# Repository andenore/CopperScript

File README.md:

# CopperScript

**PCB design as code. Hardware intent, written in code.**

CopperScript is a strongly typed language and compiler for PCB connectivity,
electrical intent, mechanical geometry and physical constraints. Describe
components, peripheral selection, nets, supply domains, board shape and placement
intent in readable `.copper` source. Check electrical rules, resolve versioned
library parts, edit mechanics and floorplans visually, and inspect experimental
routing and native KiCad exports.

[Project website](https://andenore.github.io/CopperScript/) ·
[Language reference](docs/language-reference.md) ·
[Examples](examples/README.md) ·
[CopperAssetTracker](https://github.com/andenore/CopperAssetTracker)

LLM agents: start with `copper agent-guide`, then request only the topics and
library contracts needed for the task. Contributors also follow [AGENTS.md](AGENTS.md).
The [documentation index](docs/README.md) routes tasks to current references;
[TODO.md](TODO.md) tracks unfinished work.

## More than connections

A capacitor protects a particular pin. A switching converter has a critical
current loop. A radio needs reference geometry and a return path. CopperScript
makes supported intent explicit alongside the connections, with reusable
engineering definitions and inspectable intermediate representations.

```copper
component C_MCU: CAPACITOR {
    value = 100nF;
    footprint = "Capacitor_SMD:C_0402_1005Metric";
    role = decoupling;
    decouples = "U_MCU.VDD";
}
```

This excerpt from the tracker composition associates a bypass capacitor with
its supply pin. The association survives compilation and informs generic
decoupling placement and surface-feed decisions. It is not a complete board.

## Mechanical design and constraints

Define board shape and fit in the same version-controlled source as the circuit:
rectangular, circular, polygonal and supported curved outlines; cutouts; mounting
holes and slots; placement and copper keepouts. Named datums and edge/pad
attachments locate connectors precisely. Declared component heights, enclosure
limits and assembly-access regions express supported fit requirements; pinned
DXF drawings provide read-only reference guides.

Placement constraints capture fixed position, rotation and side, allowed angles,
placement regions, distance limits, alignment and groups. Routing constraints
describe widths, clearances, permitted layers, differential pairs and length
matching. Supported constraints reach physical IR and their placement, routing
or verification consumers; reports retain unresolved requirements and external
evidence obligations.

This excerpt from [the mechanical editor demo](examples/mechanical_editor_demo/board.copper)
defines a board outline, a mounting hole and a component pose. The complete
example supplies the component declarations and nets:

```copper
mechanical {
    outline rectangle { width = 40mm; height = 30mm; }
    hole H1 {
        position = (3mm, 3mm); diameter = 2.2mm;
        head_clearance_radius = 2mm;
    }
}
constraint fixed_placement(R_ANCHOR) {
    x = 7mm; y = 8mm;
    rotation = 0; side = front;
}
```

The browser-based mechanical editor shows actual pads, courtyards, board material
and ratsnest guides. Preview automatic placement, drag or enter exact poses,
measure geometry and deliberately lock placement intent. Review the source diff
and explicitly save geometry or constraint changes back to `.copper`, with
undo/redo.
Temporary placement previews stay temporary until you save explicit intent;
imported profile definitions retain their library ownership.

```console
copper edit-mechanical examples/mechanical_editor_demo/board.copper
```

Resolve the example's real KiCad footprints before opening the editor. See
[mechanical source](docs/mechanical-language.md),
[the editor workflow](docs/mechanical-editor.md),
[reusable board profiles](docs/mechanical-profiles.md),
[constraint syntax and coverage](docs/language-reference.md#constraints) and
[VS Code setup](integrations/vscode/README.md). Supported mechanical checks do
not establish a full 3D enclosure fit or manufacturing qualification.

## See a complete design

[CopperAssetTracker](https://github.com/andenore/CopperAssetTracker) combines
an STM32 host, cellular connectivity, GNSS, Bluetooth and motion sensing on a
six-layer board. The recorded 2026-10-11 modem-power review has 91 components and
75 physical nets, with zero native DRC violations and zero unconnected items.
These are results for that recorded candidate, not a success guarantee for other
boards or a production approval. Routing remains experimental; RF, power,
battery, assembly, CAM and prototype qualification remain open.

Inspect the [snapshot provenance](site/assets/snapshot.json),
[current board status](https://github.com/andenore/CopperAssetTracker/blob/main/docs/validation.md)
and [revision reproduction guide](https://github.com/andenore/CopperAssetTracker/blob/main/revisions/modem-power-v1/README.md).
The picture is native KiCad output, not a photograph of assembled hardware.

## Three repositories, one workflow

| Repository | Owns |
| --- | --- |
| CopperScript | Language/compiler, electrical and physical checks, mechanical editor, constraint-driven placement/routing and KiCad export |
| [CopperLib](https://github.com/andenore/CopperLib) | Versioned parts, footprints, reusable circuits, mechanical profiles and engineering contracts |
| [CopperAssetTracker](https://github.com/andenore/CopperAssetTracker) | Board composition, application configuration and board-specific evidence |

CopperLib is one library provider; independent libraries use the same interfaces.

## Quick start

CopperScript is the `copper` command-line program, written in Rust. Install it
from this repository with the pinned toolchain in `rust-toolchain.toml`, or use a
release binary (the `copper-Linux` and `copper-Windows` artifacts of the
[Rust workflow](.github/workflows/rust.yml)) on your `PATH`:

```console
cargo install --locked --path crates/copper
copper agent-guide
copper check examples/valid_board/board.copper
copper compile examples/valid_board/board.copper -o build/board.json
```

For development, build and test the workspace; see the [Rust workspace](crates/README.md):

```console
cargo build --release -p copper      # target/release/copper
cargo test --workspace --release
```

Populate pinned dependencies once, then use their verified cache offline:

```console
copper check examples/full_vertical/board.copper --locked
copper check examples/full_vertical/board.copper --locked --offline
```

Dependency versions and development replacements belong in `copper.mod`;
`copper.lock` binds supported package assets. Investigate mismatched inputs
instead of silently relocking. CopperLib is one provider; other library
repositories use the same interfaces. See [managed footprints](docs/footprint-dependencies.md)
and [selective library retrieval](docs/library-context.md).

## Design and review

Use the [language reference](docs/language-reference.md) for syntax and
[examples index](examples/README.md) for complete board inputs. The
[CLI workflow](docs/cli-workflow.md) covers compilation, placement and export.

```console
copper library search "query" --project path/to/project
copper library inspect "package/path::Symbol" --project path/to/project
copper summarize build/route-report.json
```

Search declared dependencies first, then inspect selected interfaces,
requirements and evidence by section. Reports provide bounded summaries and
artifact-bound requirement coverage; see [LLM workflow](docs/llm-workflow.md).

For a complete registered board, use its shared Make targets:

```console
make EXAMPLE=full-vertical route
make EXAMPLE=cm4 route
```

The standard `route-board` pipeline owns bounded placement/package feedback,
ordinary routing and native-filled copper repair. Supply the board's actual
layers, fabrication profile, footprints and macro assets. See
[routing profiles and invariants](docs/filled-copper-feedback.md) and
[build configuration](docs/make-builds.md). Fill and DRC are CopperScript's own,
so a run needs no KiCad; KiCad 10 is the optional cross-check (`KICAD_CLI` for
`make route`, `--verify-plane-fill KICAD_CLI` for `route-board`). Outputs and
reports go into fresh build directories;
failed runs remain review drafts.

## Qualification and outputs

ERC, successful routing and zero native DRC errors are distinct from electrical,
RF/power, assembly, independent CAM and prototype qualification. Missing evidence
remains incomplete. Use [engineering qualification](docs/engineering-qualification.md),
[manufacturing files](docs/manufacturing-files.md) and
[assembly selections](docs/assembly-pinning.md) for their respective gates.

PCB export writes a same-stem `.kicad_pro`, local footprint table and footprint
library. Keep the generated directory together when sharing it; see
[KiCad project export](docs/kicad-project-export.md). Placement-only exports have
no routing copper and must not be sent for fabrication.

The CI [benchmark ladder](.github/workflows/rust.yml) routes the example and
consumer boards and publishes their results; a routed result is not approval.
Contributor internals and ERC coverage are in [compiler architecture](docs/compiler-architecture.md).

## Editor language support

The [CopperScript language server](docs/language-server.md) provides live source
checks, completion, hover, definition navigation and document outlines for
`.copper` files. Start it through an LSP client with `copper lsp`. The
[VS Code extension](integrations/vscode/README.md) includes the client, runs
`copper` from `PATH` (or a configured command) and builds offline without npm
dependencies. The separate [extension release plan](docs/extension-release-plan.md)
covers Marketplace packaging and automated releases. Analysis uses unsaved
source and the project's locked/offline imports.

## Python implementation removed

CopperScript was first implemented in Python (the `pcbir` and `copperscript`
packages). The Rust `copper` binary replaced it, and the Python code, its tests
and the porting harness were removed. The last commit with the Python
implementation is `b16122a` on `main`; consumer repositories that still pin a
Python commit use `eb92637`. The Python-only commands `audit-cam`,
`assess-engineering`, `qualification-gate` and `sim` were dropped.

## Project website

The [static project website](https://andenore.github.io/CopperScript/) introduces
the language and the tracker showcase. Its source, deployment configuration and
[publishing plan](site/README.md) live in this repository. Website validation
does not compile boards or change compiler, library or release pins.

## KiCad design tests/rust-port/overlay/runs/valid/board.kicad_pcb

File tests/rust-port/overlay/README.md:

# M6 `editor-overlay` fixtures

Build runs for the `editor-overlay` and `editor-overlay-options` comparison
suites (`scripts/compare_corpus.json`). `editor-overlay` reads a routed
build run (`run.json`, `board.kicad_pcb`, `board.editor-intent.json` and the
optional `kicad-drc.json`) and probes the saved board with KiCad's Python.
There is no Rust router yet and no KiCad in the harness, so the runs are
produced once by the Python CLI and committed, and the probe is stood in for.

Regenerate everything with

```sh
python tests/rust-port/overlay/generate.py
```

which routes each board with `route-board --routing-profile quick --locked
--offline --allow-proxy-footprints` (`PYTHONHASHSEED=0 PYTHONUTF8=1`), keeps
the draft board and the editor intent the compiler writes beside it, and
writes a `run.json` with the digests `pcbir.build` records (the real runner
needs `kicad-cli`). The harness copies a run into the case's output directory
first (the corpus `stage` field), because the command binds the overlay into
the sibling `run.json`; both implementations then start from identical copies
and the rewritten manifest is compared like any other output.

| Run | Board | What it covers |
|---|---|---|
| `flat` | `boards/flat.copper` | two front parts, one routing layer, no vias: the success path |
| `rear` | `boards/rear.copper` | rear-side parts: the native orientation differs by 180 degrees |
| `demo` | `examples/mechanical_editor_demo` | a partial route (exit 1 build) with holes and a cutout |
| `valid` | `examples/valid_board` | vias: Python compares the probe's `via_type` field against an intent without one, so every board with vias is refused as "native PCB copper does not match" (reproduced as is) |
| `verified`, `remaining` | `flat` | `kicad-drc.json` bound by digest, with no and with one remaining connection |
| `filled` | `flat` | the board plus a filled polygon the probe reads as native copper |
| `drc-unbound`, `drc-units` | `flat` | evidence present but unbound (stale report digest, inch units): no credit |
| `intent-schema`, `unbound`, `pcb-changed`, `pose-mismatch`, `copper-mismatch` | `flat` | one broken binding each |
| `duplicate-key`, `nonfinite`, `bad-json`, `missing-intent`, `manifest-list` | `flat` | malformed inputs (`manifest-list` is an uncaught Python `AttributeError`) |

`kicad-python/` holds the probe stand-ins the suites pass as
`--kicad-python`: `fake-kicad-python.sh` runs `native_probe_stub.py`, a reader
of the saved `.kicad_pcb` text that prints what the pcbnew probe prints
(layers, footprint poses, segments, vias, `filled_polygon` rings);
`failing-kicad-python.sh` exits 2 like a Python without `pcbnew`;
`garbled-kicad-python.sh` prints no JSON. The stand-in takes the board as its
last argument, because Python runs `python native_overlay.py BOARD` while the
binary runs `python -c SCRIPT BOARD`. On Windows the shell stand-ins cannot
execute and both implementations report `[WinError 193]`.

These are comparison inputs, not routing or qualification evidence; the
`kicad-drc.json` files here were written by hand, no native DRC ran.

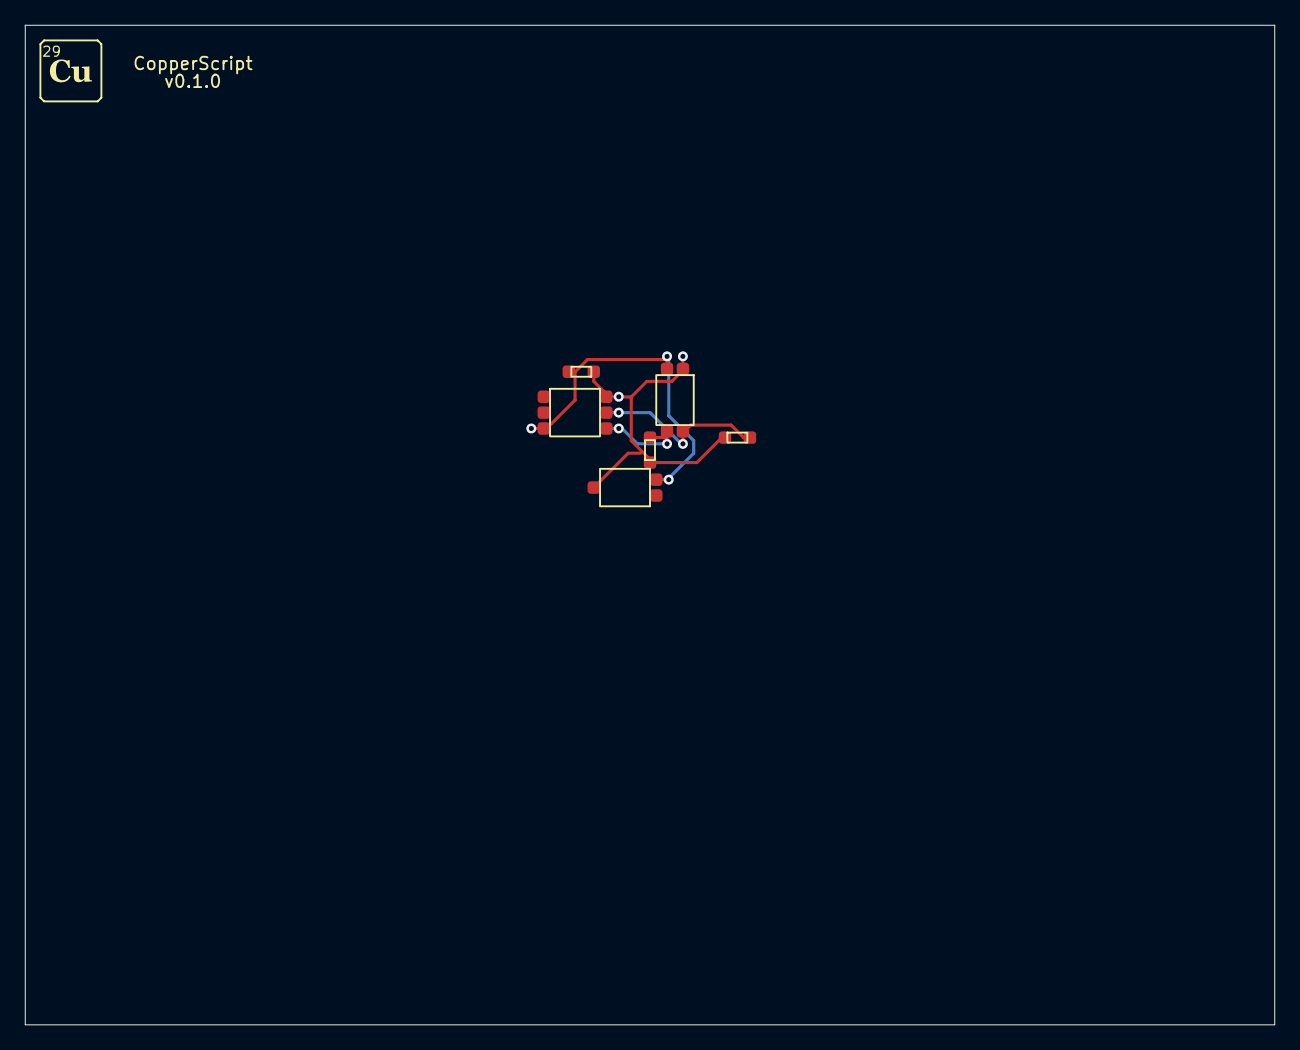
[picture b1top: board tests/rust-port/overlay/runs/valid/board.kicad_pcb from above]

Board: 2 copper layers, 100.0 x 80.0 mm, 6 parts (0 on the bottom side), 4 nets.

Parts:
C1: 100 nF; 0402_9c2134b530__0fb0bb9a2e0077d858db
R1, R2: 4.7 kohm; 0402_b4527f9b21__9b192bf2ecd33fdeea18
U1: REGULATOR_3V3; SOT_23_3_d497cde594__216aa7294530fdcf69b5
U2: STM32G0B1CBT6; LQFP_48_f42af30189__71b94d8e6008976dbf1f
U3: BME280; LGA_8_40352dfb0d__fcaac17623b50b27bffa

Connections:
GND: C1.2, U1.2, U2.23, U3.2
I2C_SCL: R2.2, U2.45, U3.3
I2C_SDA: R1.2, U2.46, U3.4
V3V3: C1.1, R1.1, R2.1, U1.3, U2.24, U3.1

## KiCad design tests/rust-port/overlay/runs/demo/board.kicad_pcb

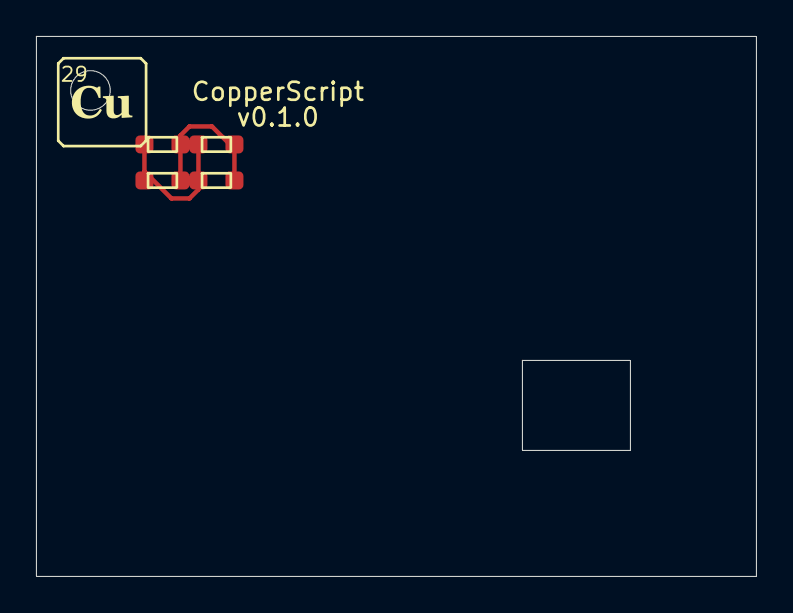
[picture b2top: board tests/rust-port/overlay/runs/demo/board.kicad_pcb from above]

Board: 2 copper layers, 40.0 x 30.0 mm, 5 parts (0 on the bottom side), 2 nets.

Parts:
C1: 100 nF; Capacitor_SMD_C_0603_1608Metric_2861610917__0449c3e1cc76e45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
CS_MH_8bf797aa02bd65b7: mechanical_hole_2200000__d5ff692c33a17c9ddffc
R1: 1 kohm; Resistor_SMD_R_0603_1608Metric_27d63fc587__56e0a9f34a377f4e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
R2: 2 kohm; Resistor_SMD_R_0603_1608Metric_27d63fc587__56e0a9f34a377f4e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
R_ANCHOR: 10 kohm; Resistor_SMD_R_0603_1608Metric_27d63fc587__56e0a9f34a377f4e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

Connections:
GND: C1.2, R1.2, R2.2, R_ANCHOR.2
SIGNAL: C1.1, R1.1, R2.1, R_ANCHOR.1

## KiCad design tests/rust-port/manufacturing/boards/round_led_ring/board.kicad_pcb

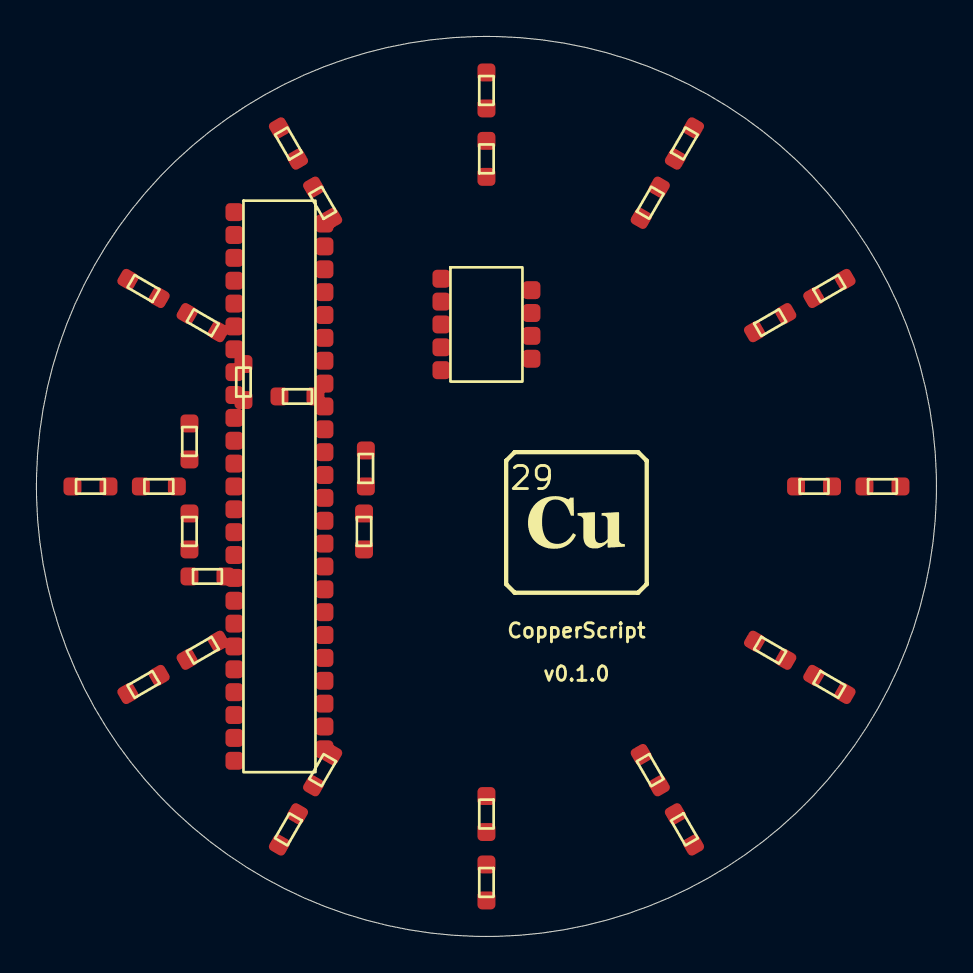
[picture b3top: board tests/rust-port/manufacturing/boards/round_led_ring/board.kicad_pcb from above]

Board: 2 copper layers, 50.0 x 50.0 mm, 34 parts (1 on the bottom side), 32 nets, no tracks yet.

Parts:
BT1: KEYSTONE_3034; github_com_andenore_CopperLib_packages_parts_keystone_3034_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
C_BULK: 4.7 uF; Capacitor_SMD_C_0603_1608Metric_2861610917__0449c3e1cc76e45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
C_DEC1: 100 nF; Capacitor_SMD_C_0402_1005Metric_2f410b0184__bb2777df16be07b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
C_DEC3: 100 pF; Capacitor_SMD_C_0402_1005Metric_2f410b0184__bb2777df16be07b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
C_DEC4: 1 uF; Capacitor_SMD_C_0603_1608Metric_2861610917__0449c3e1cc76e45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
C_VDD1, C_VDD2: 100 nF; Capacitor_SMD_C_0402_1005Metric_2f410b0184__bb2777df16be07b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
J_SWD: SWD_HEADER; Connector_Debug_FTSH_105_01_L_DV_007_K_4d35ae116d__f16acb66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
LED1, LED2, LED3, LED4, LED5, LED6, LED7, LED8, LED9, LED10, LED11, LED12: LED; LED_SMD_LED_0603_1608Metric_45d2177621__b8a31ac90f3c386e5b10
R_LED1, R_LED2, R_LED3, R_LED4, R_LED5, R_LED6, R_LED7, R_LED8, R_LED9, R_LED10, R_LED11, R_LED12: 10 kohm; Resistor_SMD_R_0603_1608Metric_27d63fc587__56e0a9f34a377f4e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
R_RESET: 10 kohm; Resistor_SMD_R_0603_1608Metric_27d63fc587__56e0a9f34a377f4e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
U1: NRF52832_QFAA; Package_DFN_QFN_QFN_48_1EP_6x6mm_P0_4mm_EP4_2x4_2mm_209eb14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

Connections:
DEC1: C_DEC1.1, U1.1
DEC3: C_DEC3.1, U1.33
DEC4: C_DEC4.1, U1.46
GND: BT1.2, C_BULK.2, C_DEC1.2, C_DEC3.2, C_DEC4.2, C_VDD1.2, C_VDD2.2, J_SWD.3, J_SWD.5, J_SWD.9, U1.31, U1.45, U1.49
LED1_A: LED1.1, R_LED1.2
LED1_K: LED1.2, U1.40
LED2_A: LED2.1, R_LED2.2
LED2_K: LED2.2, U1.38
LED3_A: LED3.1, R_LED3.2
LED3_K: LED3.2, U1.37
LED4_A: LED4.1, R_LED4.2
LED4_K: LED4.2, U1.29
LED5_A: LED5.1, R_LED5.2
LED5_K: LED5.2, U1.27
LED6_A: LED6.1, R_LED6.2
LED6_K: LED6.2, U1.23
LED7_A: LED7.1, R_LED7.2
LED7_K: LED7.2, U1.20
LED8_A: LED8.1, R_LED8.2
LED8_K: LED8.2, U1.17
LED9_A: LED9.1, R_LED9.2
LED9_K: LED9.2, U1.8
LED10_A: LED10.1, R_LED10.2
LED10_K: LED10.2, U1.5
LED11_A: LED11.1, R_LED11.2
LED11_K: LED11.2, U1.4
LED12_A: LED12.1, R_LED12.2
LED12_K: LED12.2, U1.42
RESET: J_SWD.10, R_RESET.2, U1.24
SWDCLK: J_SWD.4, U1.25
SWDIO: J_SWD.2, U1.26
VBAT: BT1.1, C_BULK.1, C_VDD1.1, C_VDD2.1, J_SWD.1, R_LED1.1, R_LED2.1, R_LED3.1, R_LED4.1, R_LED5.1, R_LED6.1, R_LED7.1, R_LED8.1, R_LED9.1, R_LED10.1, R_LED11.1, R_LED12.1, R_RESET.1, U1.13, U1.36, U1.48
